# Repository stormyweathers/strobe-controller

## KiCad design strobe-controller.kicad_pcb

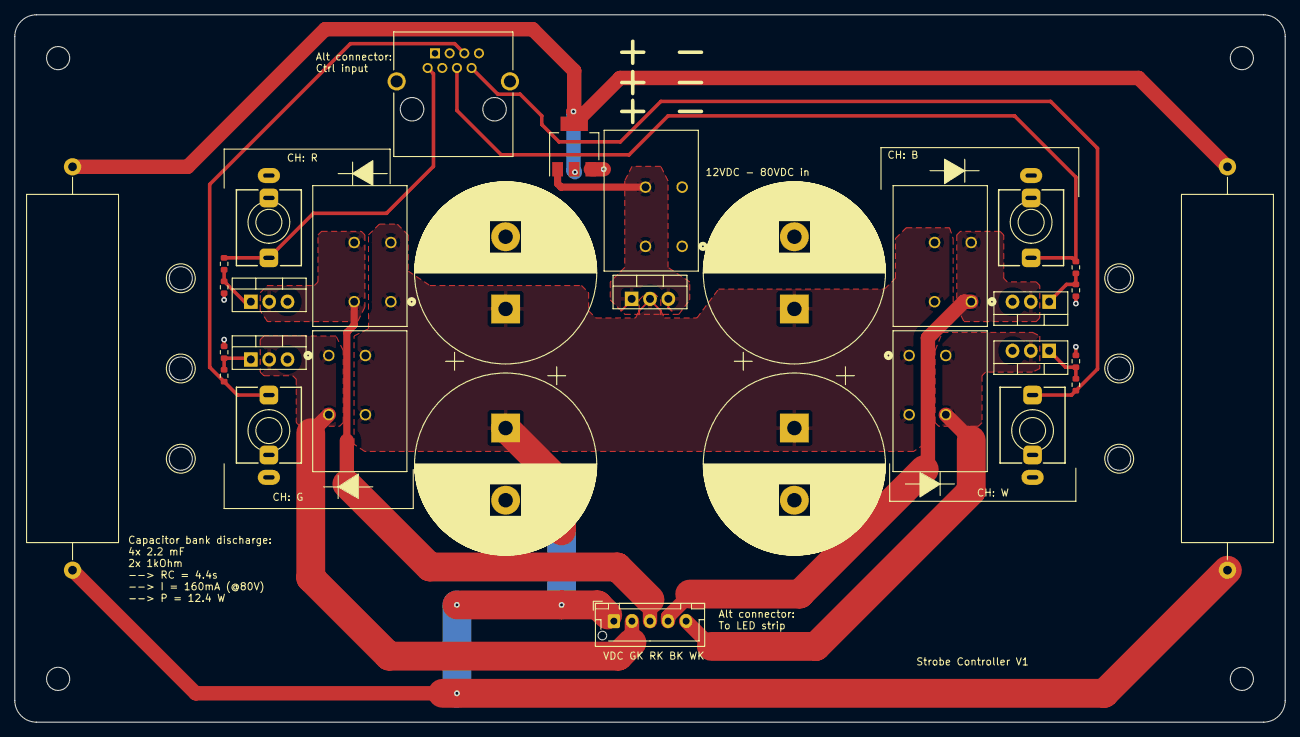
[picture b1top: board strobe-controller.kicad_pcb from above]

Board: 2 copper layers, 176.0 x 98.0 mm, 37 parts (0 on the bottom side), 16 nets.

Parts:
C201, C301, C401, C501: 2.2m; CP_Radial_D25.0mm_P10.00mm_SnapIn
CO101: RJ45
D101: LED_RGBW; JST_XH_B5B-XH-AM_1x05_P2.50mm_Vertical
D103: D_Schottky_AKA; TO-220-3_Vertical
H101, H102: MountingHole; DINRailAdapter_3xM3_PhoenixContact_1201578
H103, H104, H105, H106: MountingHole; MountingHole_3.2mm_M3_DIN965
J101: Power_in; CONN_1330710000
J102: LED_B; CONN_1330710000
J103, J105: LED_G; CONN_1330710000
J104: LED_R; CONN_1330710000
J202, J302, J402, J502: mono-jack; Jack_3.5mm_QingPu_WQP-PJ301M-12_Vertical
Q105: BSP149; SOT-223-3_TabPin2
Q201, Q301, Q401, Q501: FQP30N06L; TO-220-3_Vertical
R109, R110: 1k; R_Axial_Power_L48.0mm_W12.5mm_P55.88mm
R201, R301, R401, R501: 100R; R_0603_1608Metric
R202, R302, R402, R502: 470k; R_0603_1608Metric

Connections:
Drain_shunt: Q105.2 (D), R109.2, R110.2
GND: C201.2, C301.2, C401.2, C501.2, CO101.Bl*, CO101.Br*, CO101.Gr*, CO101.Or*, J101.1, J202.S, J302.S, J402.S, J502.S, Q105.3 (S), Q201.3 (S), Q301.3 (S), Q401.3 (S), Q501.3 (S), R202.1, R302.1, R402.1, R502.1
LED_B: CO101.Bl, J202.T, R201.1
LED_G: CO101.Gr, J402.T, R401.1
LED_R: CO101.Or, J502.T, R501.1
LED_W: CO101.Br, J302.T, R301.1
unnamed: Q201.1 (G), R201.2, R202.2
unnamed: Q301.1 (G), R301.2, R302.2
unnamed: Q401.1 (G), R401.2, R402.2
unnamed: Q501.1 (G), R501.2, R502.2
VDC: C201.1, C301.1, C401.1, C501.1, D101.1 (+V), D103.2 (K), J102.2, J103.1, J104.1, J105.2, R109.1, R110.1
Vin: D103.1 (A), D103.3 (A), J101.2, Q105.1 (G)
drain_B: D101.4 (BK), J102.1, Q201.2 (D)
drain_G: D101.2 (GK), J105.1, Q401.2 (D)
drain_R: D101.3 (RK), J104.2, Q501.2 (D)
drain_W: D101.5 (WK), J103.2, Q301.2 (D)

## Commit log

2023-09-07 init commit, layout looks good starting routing
2023-09-07 V1 for fab
2023-09-25 some din rail stuff
2023-09-25 added strobe-driver arduino code. working with multi-colored pulses and teensy timer tool
2023-09-25 started testing using the control-panel lib
2023-10-04 integrated control panel library, built control panel, made preprogrammed color paths. but there are bugs: cannot turn off strobe_timer, program freezes after a 10s of seconds, pulse code is not upda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
2023-11-02 fixed weird git submodule issue, lots of changes. Timers are working, pulled code out into a bunch of include files
2023-11-02 set up timers and control for all three instalations: fan, dance, and drip. They are all currently on the same frequency, must have mode for tuning them next
2023-11-03 started classing up each strobe channel, which has an independent timer and subchannels. not yet integrated
2023-11-03 checkpoint before integration! contruct pw timers in strobe_channel
2023-11-03 added strobe_period calculation to strobe_channel class
2023-11-03 checkpoint before integrating strobe_channel class::: include strobe_channel.h, fixed all compiletime errors, mostly to do with lambda capture in callback functions
2023-11-03 started integration, compiles and runs, see correct display. but untested with actual strobes attached
2023-11-03 reconfiguring display menu for 3-channel control
2023-11-03 reconfigured display menu working
2023-11-03 added channel control logic to menu.h, removed lots of commented out code,, needs testing
2023-11-03 fixed position counter issue in pulse decoding, tested and it works
2023-11-05 tuned preset modes, started a more advanced color transform calc in python
2023-11-05 moved update_display to menu.h
2023-11-05 got colorspace rotations and scaling working in python
2023-11-05 started implementing color transformations in arduino, but got cyclic include dependencies.. try splitting .h and .cpp
2023-11-05 moved apply transform to strobe_channel, and added transform enable and matrix to class. use joystick long button press to toggle color transforms
2023-11-05 color transforms are working! fixed pulse_code reconstruction bug that killed blue channel
2023-11-06 got color mode 1,2 woring for the fan. colormode 3 will be dynamic colors which requires transform modulation
2023-11-06 progess of fan modes, need to tune speed and implement color transform modulation
2023-11-06 got the bare NCO working, with arbitrary waveform, need to add I2C control
2023-11-06 I2C communication working between the main strobe driver and the NCO
2023-11-07 calibrated NCO, needed 6% fudge factor, got color modulation working, defined dance modes
2023-11-07 skipped precomputation stepin NCO
2023-11-07 fixed phase calc: x2pi instead of /2pi, this got rid of the 6% fudge factor to lock frequencies
2023-11-07 got coinslot logic working, added breaks to switch case for slow dance
2023-11-09 tuned fan mode speed range and arc angles
2023-11-10 tuned dance modes
2023-11-10 used color modulation for dripper modes
2023-11-22 pulse timing glitches made less frequent: update_display_flag set to false at the end of update_display(), added copious yield() to loop(). should find a way to use TIM timers instead of TCK
2023-11-22 used TMR instead of TCK timers for strobe timers, eliminated timing glitches, and i got rid of the copious yields
2024-01-03 started python implementation of advanced timing control
2024-01-03 started using nested, signed pulse train formalism. just some boilerplate for now, no pulse addition yet
2024-01-03 started implementing pulse addition in python, first few cases are working
2024-01-04 pulse addition works for all flat cases, need to fix nested case issue
2024-01-04 pulse additition works for all cases, except when new pulse extends beyond scope
2024-01-05 implemented python advanced timing with linked list instead of recursive structure. Passes all test cases
2024-01-05 used chatgpt to translate the python code to c++ for the advanced timing control. needs to be tested
2024-01-13 cleaned up until the new code compiles
2024-01-20 fan speed set to backed to floor
2024-03-17 fixed joystick button manual color issue
2024-03-17 manual color toggle works in dynamic modes, limited modes for room2room installation
2024-03-17 pulse width multiple up to 16 with slider, use left slider for modulation period
2024-03-25 added joysick-z control for a hue-shift colorspace transform, added colorspace_transform namespace and merged relevant code from strobe_channel
2024-03-25 added flicker match calibration mode thats toggled by double tapping the main button
2024-03-25 fixed arithmetic bug in hue transform caclulations, adjusted mode to no longer update ratio in room2room mode
2024-03-29 reconfigured as platformio project
2024-03-29 got platformio.ini working with compile and flash
2024-03-29 removed unused code, added copy_mat to colorspace_transformations
2024-03-29 added joystick double tap for toggling oled orientation
2024-03-29 stripped down ino file for starting the pulsetrain tests
2024-03-29 ignored ipynb checkpoints
2024-03-29 pixed pulse train bug in python and cpp: new pulse at positive tail, new pulse at end of chain
2024-03-29 fixed pointer stuff in pulse_train inializer signature
2024-03-29 added linked list print, testing AddPulse, it is currently failing
2024-03-30 reerted to signed int types in PulseTrain
2024-03-30 println in linked list printer
2024-03-30 removed static cast in max, first PulseAdd tests working. todo: build systematic test to compare to python test
2024-03-30 ipynb generates cpp header that is used for automatic testing. First 7 tests pass!, issue with trailing pulse times, and also the tester itself fails at loading test num 8
2024-03-30 PulseTrain.AddPulse() passes tests: fixed case where pulse adds onto trailing end
2024-03-31 added ClockTick method to PulseTrain class
2024-03-31 refactored AddPulse to have at most 2 levels of nesting, much more readable now, still passes 12/12 tests
2024-03-31 added end of train case to Clock Tick, got the first blinky lights working with a static pulse-train
2024-04-01 got 3 PulseTrains on the same Ticktimer, tested adding single pulses with button press. ToDo: Periodic pulse addition, measure pulse widths on scope
2024-04-01 stopped using namespace TeensyTimerTool, more explicit library references. Tested periodic pulse scheduling
2024-04-01 added toggle function to turn strobes on/off. TickTimer and PulsePeriodTimer must be on different timer channels
2024-04-03 PulseTrain: in ClockTick, free the head node pointer when it decrements to zero. fixes memory leak
2024-04-03 tested a few values for tick_period_us and strobe_period_us. tick_period_us = 5,10 gives 1.02% calibration. good enough. There is some jitter on the order of one tick period. That'll have to do for n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
2024-04-03 used voltile uint32 for Node->data, this did not affect jitter, but it still seems like the right call since these values are modified in timer callbacks
2024-04-13 new branch for villa art party, need the standalone bright RGB spotlight and the fan. Fan should switch modes and speed on its own clock
2024-04-13 control_panel.h -> ControlPanel.h because that lib has been updated
2024-04-13 offloaded strobe on/off to a separate function to make loop() more readable
2024-04-13 used encoder double press to cycle channel editing with encoder
2024-04-13 set min freq in menu, prevents period overflow, still possible to break using speed slider
2024-04-13 removed dependence on 'drip' and 'dance' channels, added dependence on 'spot' channel. used channel_list[] whenever possible
2024-04-13 cleaned up menu display a little, used 0 placeholders for 3rd channel thats not in use
2024-04-13 made new apply_mode_spot, set spot initial params in setup()
2024-04-13 had a botched comms.h file, had to recover from a previous commit. Now the apply_mode_spot and apply_mode_fan are working
2024-04-13 auto mode change, use middle slider to control period
2024-04-13 apply_mode_spot uses num/denominator to normalize strobe frequency by pulse_seq_size
2024-04-13 use global variable: pulse_width_normalization to normalize spotlight pulse width using pulse_seq_size to stablilize brightness
2024-04-13 added joystick double click for screen rotation
2024-04-13 randomized automatic mode change, but period is still constant
2024-05-09 added dependency to easing-functions library for choreography. perhaps premature...
2024-05-23 control panel library name change
2024-06-07 first test with modulation
2024-06-08 frequency control works OK, its abrupt and phase discontinuous. use flag to update period only when theres a change
2024-06-15 Reset menu mode upon launch of flicker match, so encoder actually changes the correct frequency. Use TMR timer on spot strobe_timer to access slower frequencies
